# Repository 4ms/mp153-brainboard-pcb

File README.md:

## MP153 Brainboard

This is a small PCB with an STM32MP153 microprocessor, 512MB DDR3 RAM, and a stereo codec.
It's designed for running high-end audio projects.

The processor is a dual-core Cortex-A7 at 800MHz with a 240MHz Cortex-M4 co-processor. The RAM runs up to 533MHz.
The processor supports NEON instructions, so it can be very fast for audio applications.

The brainboard is meant to plug into a larger board that has all the controls and jacks. The pinout
is similar to the Daisy Submodule, though care should be taken to confirm this before plugging into an
untested project.

Look at the schematic, under "CONNECTORS". The four 2x5 pin 0.1" headers in
that section (JA1, JB1, JC1, JD1) are the connections to your control board. 

The bare minimum connection would be to apply +12V, GND, and -12V to the appropriate pins on header JA1.
The audio inputs and outputs are on header JB1, and should be in the range of +/- 10V.

Pots or other analog inputs in the range of 0V-3.3V can be input into any ADC-IN pin (most are on JC1).
Other peripherals are available: SPI, SDMMC, UART, I2C.

The debug header is J2 and you can select SWD or JTAG. I've had better luck with JTAG, so this is the default,
but if you need to use SWD then cut the solder jumper JP1 and blob it to the NRST side.

There's an on-board USB jack, and the USB signals are on pins, so you can have a USB High Speed jack on your panel or main board (Thanks Manu!).
Don't use both at once.

For firmware, look at https://github.com/4ms/mp1-brainboard-demo and also at https://github.com/4ms/stm32mp1-baremetal

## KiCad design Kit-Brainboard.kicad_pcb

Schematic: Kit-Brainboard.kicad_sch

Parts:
AN1: Pins_01x06_RightAngle_P2.54mm_TH; Pins_1x06_P2.54mm_Horizontal_TH_CroppedSilk; Part Number TSW-106-08-T-S-RA
C1, C19, C20, C41, C47, C48, C49: 2.2uF_0603_25V; C_0603; Part Number GRM188R6YA225KA12D; JLCPCB ID C57895
C2, C12, C21, C30, C40, C42, C43, C61, C64, C67, C68, C69, C82, C87, C92, C93, C94, C95, C98, C99, C102, C103, C106: 100nF_0402_16V; C_0402; Part Number GCM155R71C104KA55D; JLCPCB ID C1525
C3, C44, C81, C83: 10uF_0603_10V; C_0603; Part Number GRM188R61A106KE69D; JLCPCB ID C19702
C4: 22uF_0805_10V; C_0805; Part Number LMK212BBJ226MG-T; JLCPCB ID C45783
C5: 0.1uF_0603_16V; C_0603; Part Number 0603YC104KAT2A; JLCPCB ID C14663
C6, C7: 820pF_0402_10v; C_0402; Part Number 0402ZC821KAT2A; JLCPCB ID C565563
C8, C9, C10, C11: 180pF_0402_25V; C_0402; Part Number GRM1555C2A181JE01D; JLCPCB ID C106999
C13, C14: 6.8pF_0402_25V; C_0402; Part Number CC0402CRNPO9BN6R8; JLCPCB ID C1576
C15, C16, C17, C18, C24, C25, C26, C27, C28, C34, C35, C36, C37, C38, C39: 10nF_0402_16V; C_0402; Part Number CC0402KRX7R7BB103; JLCPCB ID C15195
C22, C23: 220pF_0402_50V; C_0402; Part Number AC0402JPNPO9BN221; JLCPCB ID C327000
C29, C32: 2.2uF_0402_6.3V; C_0402; Part Number GRM155R60J225KE95D; JLCPCB ID C12530
C31, C33, C45, C46, C50, C51, C52, C53, C54, C55, C59, C60, C62, C63, C70, C73, C79, C109: 1uF_0402_25V; C_0402; Part Number GMK105CC6105KV-F; JLCPCB ID C52923
C56, C57, C58, C65, C66, C72, C75, C77, C78, C85, C86, C96, C97, C100, C101, C104, C105, C107, C108: 100nF_0402_50V; C_0402; Part Number GRM155R71H104KE14D; JLCPCB ID C307331
C71, C74, C80: 3.3nF_0402_16V; C_0402; Part Number VJ0402Y332KXACW1BC; JLCPCB ID C26404
C76, C84: 4.7uF_0402_6.3V; C_0402; Part Number GRM155R60J475ME47; JLCPCB ID C23733
C88, C89, C90, C91: 22uF_0603_6.3V; C_0603; Part Number GRM188R60J226MEA0J; JLCPCB ID C59461
D1, D2, D3, D4, D5, D6, D7, D8, D9, D10, D12, D13, D14, D15, D16, D17, D18, D19, D20, D21, D22, D23, D24, D25: BAT54S; SOT23-3_PO132; Part Number BAT54S-7-F; JLCPCB ID C83574
D11: BAT54LP; DFN-1006-2; Part Number BAT54LP-7; JLCPCB ID C134410
J1: Pins_02x04_RightAngle_P2.54mm_TH; Pins_2x04_P2.54mm_Horizontal_CroppedSilk; Part Number TSW-104-08-T-D-RA
J2: Pins_02x05_P1.27mm_SMT; Pins_2x05_1.27mm_SMD; Part Number FTSH-105-01-F-DV
J3: USB_B_Micro_10118194-0011LF; USB_Micro-B_Amphenol_10118194_Horizontal; Part Number 10118194-0011LF
JA1: Pins_02x05_P2.54mm_SMT; PinHeader_2x05_P2.54mm_Vertical_SMD; Part Number TSM-105-01-F-DV
JB1: Pins_02x05_P2.54mm_SMT; PinHeader_2x05_P2.54mm_Vertical_SMD; Part Number TSM-105-01-F-DV
JC1: Pins_02x05_P2.54mm_SMT; PinHeader_2x05_P2.54mm_Vertical_SMD; Part Number TSM-105-01-F-DV
JD1: Conn_02x06_Odd_Even; PinHeader_2x06_P2.54mm_Vertical_SMD
JP1: SolderJumper_3_Bridged12; JUMPER_SMD_1x3_tiny
L1, L3: 1uH_3.2A_2520; L_1008_2520Metric; Part Number DFE252012P-1R0M=P2; JLCPCB ID C435392
L2: 4.7uH_1.7A_2510; L_Wuerth_MAPI-2510; Part Number SRN2510F-4R7M; JLCPCB ID C2047781
NT1, NT2: NetTie_2; NetTie-2_SMD_Pad0.16mm_6mil
PCB1: PCB; Part Number brainboard-mp1-v1.0
Q1: MMBT3904; SOT23-3_PO132; Part Number MMBT3904-TP; JLCPCB ID C20526
R1, R2: 4.7k_0402; R_0402; Part Number RC0402FR-074K7L; JLCPCB ID C105871
R3: 3k_0402; R_0402; Part Number RC0402FR-073KL; JLCPCB ID C137987
R4: 430k_0402; R_0402; Part Number RC0402FR-07430KL; JLCPCB ID C163463
R5: 620k_0402; R_0402; Part Number RC0402FR-07620KL; JLCPCB ID C137952
R6, R7, R8, R9, R10, R11, R13, R14, R30, R35, R36, R37, R38, R41, R46, R47, R48, R49, R50, R51, R61, R64, R66, R67, R69, R72, R74: 10k_0402; R_0402; Part Number RC0402FR-0710KL; JLCPCB ID C60490
R12, R15, R16, R17: 24k_0402; R_0402; Part Number RC0402FR-0724KL; JLCPCB ID C138026
R18, R19, R26, R27, R39, R40, R70, R71: 1k_0402; R_0402; Part Number RC0402FR-071KL; JLCPCB ID C106235
R20, R21, R22, R23, R24, R25: 2k_0402; R_0402; Part Number RC0402FR-072KL; JLCPCB ID C60488
R28, R29: 1M_0402; R_0402; Part Number RC0402FR-071ML; JLCPCB ID C138033
R31, R32, R60, R73: 100k_0402; R_0402; Part Number RC0402FR-07100KL; JLCPCB ID C60491
R33, R34: 14k_0402; R_0402; Part Number RC0402FR-0714KL; JLCPCB ID C327372
R42, R43, R44, R45, R53, R54, R55, R56, R57, R58: 68Ω_0402; R_0402; Part Number RC0402FR-0768RL; JLCPCB ID C163455
R52, R59: 240Ω_0402; R_0402; Part Number RC0402FR-07240RL; JLCPCB ID C114755
R62: 20k_0402; R_0402; Part Number RC0402FR-0720KL; JLCPCB ID C93942
R63: 31.6k_0402; R_0402; Part Number RC0402FR-0731K6L; JLCPCB ID C276265
R65: 6.8k_0402; R_0402; Part Number RC0402FR-076K8L; JLCPCB ID C93940
R68: 100Ω_0402; R_0402; Part Number RC0402FR-07100RL; JLCPCB ID C106232
S1, S2, S3: SW_Push_PTS526 SM15 SMTR2 LFS; Button_Tact_PTS526; Part Number PTS526 SM15 SMTR2 LFS
SJ1, SJ2: Shunt Jumper; Part Number LL1044-1B
U1: PCM3060PW; TSSOP-28_4.4x9.7mm_P0.65mm; Part Number PCM3060PW
U2: STM32MP15xxAD; TFBGA-257_10x10mm_perP0.5_cntrP0.65; Part Number STM32MP153DAD; JLCPCB ID C1236719
U3: USBLC6-2SC6; SOT-23-6; Part Number USBLC6-2SC6; JLCPCB ID C2827654
U4, U6, U7, U8, U9, U10, U11, U12: NJM2068; TSSOP-8_4.4x3mm_Pitch0.65mm; Part Number NJM2068V-TE1
U5: NORFLASH_W25Q128JV; SOIC-8_5.28x4.9mm_Pitch1.27mm; Part Number W25Q128JVSIQ; JLCPCB ID C113767
U13: NCP51460SN33; SOT23-3_PO132; Part Number NCP51460SN33T1G; JLCPCB ID C233715
U14: DDR3L-RAM-4Gb_MT41K256M16TW; FBGA-96_Layout2x3x16_Body8x14_P0.8mm; Part Number MT41K256M16TW-107-P-V00H; JLCPCB ID C253882
U15, U16, U17: AP6230xZ6; SOT-563; Part Number AP62301Z6
U18, U19: TAR5S33; SOT-23-5; Part Number TAR5S33TE85LF; JLCPCB ID C2762700
U20: AP2411SN; DFN-6-1EP_2x2mm_P0.65mm_EP1x1.6mm; Part Number AP2411SN-7; JLCPCB ID C2149815
V1: AP2120N-5.0TRG1; SOT23-3_PO132; Part Number AP2120N-5.0TRG1
X1: 24MHz_8pF_2x1.6mm; Crystal_2.0x1.6mm_4pin; Part Number ECS-240-8-37-CKM-TR3; JLCPCB ID C1986107

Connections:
+3V3: C2.1, C12.1, C90.2, D1.2 (cathode), D2.2 (cathode), D3.2 (cathode), D4.2 (cathode), D5.2 (cathode), D6.2 (cathode), D7.2 (cathode), D8.2 (cathode), D9.2 (cathode), D10.2 (cathode), D12.2 (cathode), D13.2 (cathode), D14.2 (cathode), D15.2 (cathode), D16.2 (cathode), D17.2 (cathode), D18.2 (cathode), D19.2 (cathode), D20.2 (cathode), D21.2 (cathode), D22.2 (cathode), D23.2 (cathode), D24.2 (cathode), D25.2 (cathode), L2.2, R1.2, R2.2, R63.2, U1.7 (VDD), U5.8 (VCC)
+5VA: C3.1, U1.24 (VCC), V1.2 (VO)
+12V: C1.1, C41.1, C45.2, C46.2, C47.2, C48.2, C49.2, C57.1, C58.1, C77.1, C78.1, C96.1, C97.1, C104.1, C105.1, JA1.9, R60.1, U4.8 (V+), U6.8 (V+), U7.8 (V+), U8.8 (V+), U9.8 (V+), U10.8 (V+), U11.8 (V+), U12.8 (V+), U13.1 (VI), U15.1 (VIN), U16.1 (VIN), U17.1 (VIN), U18.5 (IN), U19.5 (IN), V1.3 (VI)
-12VA: C65.1, C66.1, C85.1, C86.1, C100.1, C101.1, C107.1, C108.1, JA1.1, U4.4 (V-), U6.4 (V-), U7.4 (V-), U8.4 (V-), U9.4 (V-), U10.4 (V-), U11.4 (V-), U12.4 (V-)
/A0: AN1.5, U2.1J1 (PA4)
/A1: AN1.2, U2.1H1 (PA5)
/A2: R44.2, U2.T3 (PA2)
/A3: R45.2, U2.W3 (PA6)
/A4: R53.2, U2.N2 (PA3)
/A5: R54.2, U2.W2 (PA7)
/A6: R55.2, U2.U2 (PB0)
/A7: R56.2, U2.V1 (PC5)
/A8: R57.2, U2.P3 (PC3)
/A9: R58.2, U2.U4 (PC0)
/ADC-IN0_DAC-OUT0: JC1.1, R35.1
/ADC-IN1_DAC-OUT1: JC1.2, R36.1
/ADC-IN2: JC1.3, R37.1
/ADC-IN3: JC1.4, R38.1
/ADC-IN4: JC1.5, R46.1
/ADC-IN5: JC1.6, R47.1
/ADC-IN6: JC1.7, R48.1
/ADC-IN7: JC1.8, R49.1
/ADC-IN8: JC1.9, R50.1
/ADC-IN9: JC1.10, R51.1
/AUDIO_IN1: JB1.7, R27.2
/AUDIO_IN2: JB1.5, R26.2
/AUDIO_OUT1: JB1.3, R18.1
/AUDIO_OUT2: JB1.1, R19.1
/BOOT0: R30.2, R73.1, S1.3, S1.4, U2.H3 (BOOT0)
/BOOT2: Q1.3 (C), R74.2, U2.H1 (BOOT2)
/CODEC_RESET: U1.15 (~RST), U2.C1 (PE12)
/D0: C15.1, D1.3 (AK), R20.2, U2.C6 (PA9)
/D1: C16.1, D2.3 (AK), R21.2, U2.E3 (PE13)
/D2: C17.1, D3.3 (AK), R22.2, U2.A3 (PB7)
/D3: C18.1, D4.3 (AK), R23.2, U2.B6 (PB4)
/D4: JD1.8, U2.1A5 (PD2)
/D5: D23.3 (AK), JD1.1, U2.U15 (PA11)
/D6: D18.3 (AK), JD1.2, U2.U5 (PB10)
/D7: D22.3 (AK), JD1.6, U2.P2 (PC2)
/D8: D20.3 (AK), JD1.4, U2.T2 (PC1)
/D9: JD1.10, U2.1B4 (PC12)
/D10: D5.3 (AK), R24.2, U2.B8 (PA8)
/D11: D25.3 (AK), JA1.3, U2.U1 (PB1)
/D12: D6.3 (AK), R25.2, U2.A10 (PE4)
/D13: D19.3 (AK), JB1.8, U2.A2 (PD1)
/D14: D24.3 (AK), JA1.5, U2.T1 (PA1)
/D15: D21.3 (AK), JB1.6, U2.C5 (PD0)
/D16: JD1.9, U2.A9 (PC8)
/D17: JD1.7, U2.B9 (PC9)
/D18: JD1.5, U2.B10 (PC10)
/D19: JD1.3, U2.C11
/D-IN0: JB1.2, R20.1
/D-IN1: JB1.4, R21.1
/D-IN2: JB1.10, R22.1
/D-IN3: JB1.9, R23.1
/D-IN10: JA1.4, R24.1
/D-IN12: JA1.6, R25.1
/DDR_A0: U2.G18 (DDR_A0), U14.N3 (A0)
/DDR_A1: U2.M19 (DDR_A1), U14.P7 (A1)
/DDR_A2: U2.F17 (DDR_A2), U14.P3 (A2)
/DDR_A3: U2.F19 (DDR_A3), U14.N2 (A3)
/DDR_A4: U2.R17 (DDR_A4), U14.P8 (A4)
/DDR_A5: U2.1C9 (DDR_A5), U14.P2 (A5)
/DDR_A6: U2.1G9 (DDR_A6), U14.R8 (A6)
/DDR_A7: U2.1A9 (DDR_A7), U14.R2 (A7)
/DDR_A8: U2.T17 (DDR_A8), U14.T8 (A8)
/DDR_A9: U2.E18 (DDR_A9), U14.R3 (A9)
/DDR_A10: U2.M17 (DDR_A10), U14.L7 (A10/AP)
/DDR_A11: U2.N19 (DDR_A11), U14.R7 (A11)
/DDR_A12: U2.M18 (DDR_A12), U14.N7 (A12/BC#)
/DDR_A13: U2.E17 (DDR_A13), U14.T3 (A13)
/DDR_A14: U2.N18 (DDR_A14), U14.T7 (A14)
/DDR_BA0: U2.G19 (DDR_BA0), U14.M2 (BA0)
/DDR_BA1: U2.P18 (DDR_BA1), U14.N8 (BA1)
/DDR_BA2: U2.H17 (DDR_BA2), U14.M3 (BA2)
/DDR_CASN: U2.J19 (DDR_CASN), U14.K3 (CAS#)
/DDR_CKE: R67.2, U2.P17 (DDR_CKE), U14.K9 (CKE)
/DDR_CLK_N: R68.2, U2.K18 (DDR_CLKN), U14.K7 (CK#)
/DDR_CLK_P: R68.1, U2.L17 (DDR_CLKP), U14.J7 (CK)
/DDR_CSN: U2.J17 (DDR_CSN), U14.L2 (CS#)
/DDR_DQ0: U2.A17 (DDR_DQ0), U14.C3 (DQU1)
/DDR_DQ1: U2.A18 (DDR_DQ1), U14.C2 (DQU3)
/DDR_DQ2: U2.C18 (DDR_DQ2), U14.A7 (DQU4)
/DDR_DQ3: U2.B16 (DDR_DQ3), U14.A3 (DQU7)
/DDR_DQ4: U2.D18 (DDR_DQ4), U14.B8 (DQU6)
/DDR_DQ5: U2.D19 (DDR_DQ5), U14.C8 (DQU2)
/DDR_DQ6: U2.C19 (DDR_DQ6), U14.D7 (DQU0)
/DDR_DQ7: U2.B17 (DDR_DQ7), U14.A2 (DQU5)
/DDR_DQ8: U2.R18 (DDR_DQ8), U14.F2 (DQL2)
/DDR_DQ9: U2.U19 (DDR_DQ9), U14.E3 (DQL0)
/DDR_DQ10: U2.T19 (DDR_DQ10), U14.G2 (DQL6)
/DDR_DQ11: U2.W18 (DDR_DQ11), U14.F7 (DQL1)
/DDR_DQ12: U2.W17 (DDR_DQ12), U14.H8 (DQL5)
/DDR_DQ13: U2.T18 (DDR_DQ13), U14.H3 (DQL4)
/DDR_DQ14: U2.U17 (DDR_DQ14), U14.H7 (DQL7)
/DDR_DQ15: U2.V17 (DDR_DQ15), U14.F8 (DQL3)
/DDR_DQM0: U2.C17 (DDR_DQM0), U14.D3 (DMU)
/DDR_DQM1: U2.V18 (DDR_DQM1), U14.E7 (DML)
/DDR_DQS0_N: U2.B18 (DDR_DQS0N), U14.B7 (DQSU#)
/DDR_DQS0_P: U2.B19 (DDR_DQS0P), U14.C7 (DQSU)
/DDR_DQS1_N: U2.U18 (DDR_DQS1N), U14.G3 (DQSL#)
/DDR_DQS1_P: U2.V19 (DDR_DQS1P), U14.F3 (DQSL)
/DDR_ODT: U2.H18 (DDR_ODT), U14.K1 (ODT)
/DDR_RASN: U2.1E9 (DDR_RASN), U14.J3 (RAS#)
/DDR_RESETN: R69.2, U2.C16 (DDR_RESETN), U14.T2 (RESET#)
/DDR_WEN: U2.J18 (DDR_WEN), U14.L3 (WE#)
/DEBUG2: J1.5, U2.D1 (PG12)
/DEBUG3: J1.7, U2.D2 (PE11)
/DFU_BOOT: R72.1, S3.4, U2.E1 (PD8)
/FLASH_CLK: U2.1J7 (PF10), U5.6 (CLK)
/FLASH_CS: U2.W11 (PB6), U5.1 (~CS)
/FLASH_IO0: U2.V8 (PF8), U5.5 (IO0/SI)
/FLASH_IO1: U2.V9 (PF9), U5.2 (IO1/SO)
/FLASH_IO2: U2.W7 (PF7), U5.3 (IO2/~WP)
/FLASH_IO3: U2.U10 (PF6), U5.7 (IO3/~HOLD/~RESET)
/I2C2_SCL: R1.1, U1.1 (MC/SCL/FMT), U2.B3 (PD7)
/I2C2_SDA: R2.1, U1.2 (MD/SDA/DEMP), U2.B1 (PG15)
/IN-L: R40.2, U1.25 (VINL)
/IN-R: R39.2, U1.26 (VINR)
/JTCK_SWCLK: J2.4, U2.A16 (JTCK-SWCLK)
/JTDI: J2.8, U2.B15 (JTDI)
/JTDO_SWO: J2.6, U2.A15 (JTDO-TRACESWO)
/JTMS_SWDIO: J2.2, U2.C15 (JTMS-SWDIO)
/JTRST: JP1.1 (A), U2.B14 (NJTRST)
/LIN+: R6.1, U1.20 (VOUTL+)
/LIN-: R7.1, U1.19 (VOUTL-)
/NRST: C21.2, D11.1 (K), JP1.3 (B), S2.3, S2.4, U2.E2 (NRST)
/NRST_CORE: C24.2, U2.J3 (NRST_CORE)
/PWR_ON: R41.1, U2.M2 (PWR_ON), U15.5 (EN)
/PWR_ONRST: D11.2 (A), R41.2, U16.5 (EN), U17.5 (EN)
/RIN+: R8.1, U1.18 (VOUTR+)
/RIN-: R9.1, U1.17 (VOUTR-)
/SAI_FS: U1.4 (LRCK1), U1.11 (LRCK2), U2.U14 (PD12)
/SAI_MCLK: U1.6 (SCKI1), U1.9 (SCKI2), U2.C2 (PE0)
/SAI_SCK: U1.5 (BCK1), U1.10 (BCK2), U2.U13 (PD13)
/SAI_SD_A: U1.12 (DIN), U2.U8 (PD11)
/SAI_SD_B: U1.3 (DOUT), U2.U7 (PG10)
/UART_RX: J1.3, U2.C10 (PC7)
/UART_TX: J1.1, U2.A4 (PC6)
/USB_HS_DM: U2.W10 (USB_DM2), U3.3 (I/O2)
/USB_HS_DP: U2.V10 (USB_DP2), U3.1 (I/O1)
/USB_RREF: R3.2, U2.1J8 (USB_RREF)
/USB_VBUS: R4.2, R5.1, U2.V16 (OTG_VBUS)
/USB_VBUS_JACK: J3.1 (VBUS), R4.1, U3.5 (VBUS)
/VCOM: C4.1, C5.1, U1.21 (VCOM), U6.5 (+), U7.5 (+)
GND: C2.2, C12.2, C13.1, C14.1, C15.2, C16.2, C17.2, C18.2, C21.1, C24.1, C25.2, C26.2, C27.2, C28.2, C29.1, C32.1, C34.2, C35.2, C36.2, C37.2, C38.2, C39.2, C40.1, C42.2, C43.2, C46.1, C47.1, C48.1, C49.1, C50.1, C51.1, C52.1, C53.1, C54.1, C55.1, C56.2, C57.2, C58.2, C59.1, C60.1, C61.1, C62.1, C63.1, C64.1, C65.2, C66.2, C70.1, C71.2, C73.1, C74.2, C75.2, C76.1, C77.2, C78.2, C79.1, C80.2, C81.1, C82.1, C83.1, C85.2, C86.2, C87.1, C88.1, C89.1, C90.1, C91.1, C92.2, C93.1, C94.2, C95.1, C96.2, C97.2, C98.2, C99.2, C100.2, C101.2, C102.2, C103.2, C104.2, C105.2, C106.2, C107.2, C108.2, C109.1, D1.1 (Anode), D2.1 (Anode), D3.1 (Anode), D4.1 (Anode), D5.1 (Anode), D6.1 (Anode), D7.1 (Anode), D8.1 (Anode), D9.1 (Anode), D10.1 (Anode), D12.1 (Anode), D13.1 (Anode), D14.1 (Anode), D15.1 (Anode), D16.1 (Anode), D17.1 (Anode), D18.1 (Anode), D19.1 (Anode), D20.1 (Anode), D21.1 (Anode), D22.1 (Anode), D23.1 (Anode), D24.1 (Anode), D25.1 (Anode), J1.2, J1.4, J1.6, J1.8, J2.3, J2.5, J2.9, J3.5 (GND), J3.6 (Shield), JA1.7, NT1.2, NT2.2, Q1.2 (E), R3.1, R5.2, R28.2, R29.2, R52.2, R59.1, R62.1, R64.1, R66.1, R67.1, R69.1, R71.2, R72.2, S1.1, S1.2, S2.1, S2.2, U1.8 (DGND), U1.27 (~MS/ADR/IFMD), U1.28 (MODE), U2.1A6 (VSS), U2.1B8 (VSS), U2.1C3 (VSS), U2.1C5 (VSS), U2.1C7 (VSS), U2.1D2 (VSS), U2.1D4 (VSS), U2.1D6 (VSS), U2.1E3 (VSS), U2.1E5 (VSS), U2.1E7 (VSS), U2.1F4 (VSS), U2.1F6 (VSS), U2.1G2 (VSS), U2.1G5 (VSS), U2.1G7 (VSS), U2.1H2 (VSS), U2.1H3 (VSS), U2.1H4 (VSS), U2.1H6 (VSS), U2.1H8 (VSS), U2.1J5 (VSS), U2.1J9 (VSS), U2.A1 (VSS), U2.A6 (VSS), U2.A19 (VSS), U2.C14 (VSS), U2.D17 (VSS), U2.F3 (VSS), U2.F18 (VSS), U2.G1 (VSS), U2.G17 (VSS), U2.K3 (BOOT1), U2.K17 (VSS), U2.K19 (VSS), U2.N1 (VSS), U2.N17 (VSS), U2.R19 (VSS), U2.U9 (VSS), U2.U11 (BYPASS_REG1V8), U2.W1 (VSS), U2.W5 (VSS), U2.W13 (VSS), U2.W19 (VSS), U3.2 (GND), U5.4 (GND), U14.A9 (VSS), U14.B1 (VSSQ), U14.B3 (VSS), U14.B9 (VSSQ), U14.D1 (VSSQ), U14.D8 (VSSQ), U14.E1 (VSS), U14.E2 (VSSQ), U14.E8 (VSSQ), U14.F9 (VSSQ), U14.G1 (VSSQ), U14.G8 (VSS), U14.G9 (VSSQ), U14.J2 (VSS), U14.J8 (VSS), U14.M1 (VSS), U14.M9 (VSS), U14.P1 (VSS), U14.P9 (VSS), U14.T1 (VSS), U14.T9 (VSS), U15.3 (GND), U16.3 (GND), U17.3 (GND), U19.2 (GND), U20.2 (GND), U20.7 (EP), X1.2, X1.4
GNDA: C1.2, C3.2, C4.2, C5.2, C9.1, C11.1, NT1.1, R12.1, R15.1, U1.16 (SGND), U1.22 (AGND2), U1.23 (AGND1), V1.1 (GND)
GNDADC: C30.2, C31.1, C33.1, C41.2, C44.2, C45.1, C72.2, C84.1, JA1.8, NT2.1, U2.1G1 (VSSA), U13.3 (GND), U18.2 (GND)
unnamed: AN1.1, C26.1, D8.3 (AK), R36.2, U8.5 (+)
unnamed: AN1.3, R43.2
unnamed: AN1.4, C25.1, D7.3 (AK), R35.2, U8.3 (+)
unnamed: AN1.6, R42.2
unnamed: C6.1, R6.2, R10.2, R16.2
unnamed: C6.2, R7.2, R11.2, R12.2
unnamed: C7.1, R8.2, R13.2, R17.2
unnamed: C7.2, R9.2, R14.2, R15.2
unnamed: C8.1, R16.1, R18.2, U4.1
unnamed: C10.1, R17.1, R19.2, U4.7
unnamed: C19.1, R32.2
unnamed: C20.1, R31.2
unnamed: C22.1, R33.1, R39.1, U7.7
unnamed: C23.1, R34.1, R40.1, U6.7
unnamed: C27.1, D9.3 (AK), R37.2, U9.3 (+)
unnamed: C28.1, D10.3 (AK), R38.2, U9.5 (+)
unnamed: C34.1, D12.3 (AK), R46.2, U10.3 (+)
unnamed: C35.1, D13.3 (AK), R47.2, U10.5 (+)
unnamed: C36.1, D14.3 (AK), R48.2, U11.3 (+)
unnamed: C37.1, D15.3 (AK), R49.2, U11.5 (+)
unnamed: C38.1, D16.3 (AK), R50.2, U12.3 (+)
unnamed: C39.1, D17.3 (AK), R51.2, U12.5 (+)
unnamed: J2.10, JP1.2 (C)
unnamed: Q1.1 (B), R73.2
unnamed: C13.2, U2.H2 (PH0-OSC_IN), X1.3
unnamed: C14.2, U2.J2 (PH1-OSC_OUT), X1.1
unnamed: C29.2, U2.1J6 (VDDA1V1_REG)
unnamed: R52.1, U2.1A8 (DDR_ZQ)
unnamed: C9.2, R11.1, U4.3 (+)
unnamed: C8.2, R10.1, U4.2 (-)
unnamed: C11.2, R14.1, U4.5 (+)
unnamed: C10.2, R13.1, U4.6 (-)
unnamed: R27.1, R29.1, U6.3 (+)
unnamed: C19.2, U6.1, U6.2 (-)
unnamed: C23.2, R32.1, R34.2, U6.6 (-)
unnamed: R26.1, R28.1, U7.3 (+)
unnamed: C20.2, U7.1, U7.2 (-)
unnamed: C22.2, R31.1, R33.2, U7.6 (-)
unnamed: R42.1, U8.1, U8.2 (-)
unnamed: R43.1, U8.6 (-), U8.7
unnamed: R44.1, U9.1, U9.2 (-)
unnamed: R45.1, U9.6 (-), U9.7
unnamed: R53.1, U10.1, U10.2 (-)
unnamed: R54.1, U10.6 (-), U10.7
unnamed: R55.1, U11.1, U11.2 (-)
unnamed: R56.1, U11.6 (-), U11.7
unnamed: R57.1, U12.1, U12.2 (-)
unnamed: R58.1, U12.6 (-), U12.7
unnamed: R59.2, U14.L8 (ZQ)
unnamed: C67.2, U15.4 (BST)
unnamed: R61.1, R62.2, U15.6 (FB)
unnamed: C67.1, L1.1, U15.2 (SW)
unnamed: C68.2, U16.4 (BST)
unnamed: R63.1, R64.2, U16.6 (FB)
unnamed: C68.1, L2.1, U16.2 (SW)
unnamed: C69.2, U17.4 (BST)
unnamed: R65.1, R66.2, U17.6 (FB)
unnamed: C69.1, L3.1, U17.2 (SW)
unnamed: C72.1, U18.3 (Noise)
unnamed: C56.1, R60.2, U19.1 (EN)
unnamed: C75.1, U19.3 (Noise)
USB_DM: J3.2 (D-), JD1.12, U3.4 (I/O2)
USB_DP: J3.3 (D+), JD1.11, U3.6 (I/O1)
VDD: C51.2, C54.2, C60.2, C63.2, C88.2, J2.1, R30.1, R74.1, S3.1, U2.1D1 (VBAT), U2.1E2 (VDD), U2.1F3 (VDD), U2.1G3 (VDD), U2.1G4 (VDD), U2.1J3 (VDD), U2.K2 (PDR_ON_CORE), U2.L3 (PDR_ON), U18.1 (EN), U19.4 (OUT), U20.1 (IN)
VDDA: C30.1, C31.2, C84.2, U2.1F1 (VDDA), U2.1F2 (VDDA), U18.4 (OUT)
VDDA_1V8: C32.2, U2.1H5 (VDDA1V8_REG), U20.3 (EN)
VDD_CORE: C50.2, C53.2, C59.2, C62.2, C70.2, C73.2, C79.2, C89.2, L1.2, R61.2, U2.1B3 (VDDCORE), U2.1B5 (VDDCORE), U2.1C4 (VDDCORE), U2.1C6 (VDDCORE), U2.1D3 (VDDCORE), U2.1D5 (VDDCORE), U2.1D7 (VDDCORE), U2.1E4 (VDDCORE), U2.1E6 (VDDCORE), U2.1E8 (VDDCORE), U2.1F5 (VDDCORE), U2.1F7 (VDDCORE), U2.1G6 (VDDCORE), U2.1G8 (VDDCORE)
VDD_DDR: C52.2, C55.2, C61.2, C64.2, C71.1, C74.1, C80.1, C81.2, C82.2, C83.2, C87.2, C91.2, C92.1, C93.2, C94.1, C95.2, C98.1, C99.1, C102.1, C103.1, C106.1, L3.2, R65.2, R70.1, U2.1B9 (VDDQ_DDR), U2.1D9 (VDDQ_DDR), U2.1F9 (VDDQ_DDR), U2.1H9 (VDDQ_DDR), U14.A1 (VDDQ), U14.A8 (VDDQ), U14.B2 (VDD), U14.C1 (VDDQ), U14.C9 (VDDQ), U14.D2 (VDDQ), U14.D9 (VDD), U14.E9 (VDDQ), U14.F1 (VDDQ), U14.G7 (VDD), U14.H2 (VDDQ), U14.H9 (VDDQ), U14.K2 (VDD), U14.K8 (VDD), U14.N1 (VDD), U14.N9 (VDD), U14.R1 (VDD), U14.R9 (VDD)
VDD_USB: C76.2, U2.1H7 (VDD3V3_USB), U20.5 (OUT)
VREF+: C33.2, C44.1, JA1.2, U2.M3 (VREF+), U13.2 (VO)
VREF_DDR: C40.2, C42.1, C43.1, C109.2, R70.2, R71.1, U2.W16 (DDR_VREF), U14.H1 (VREFDQ), U14.M8 (VREFCA)

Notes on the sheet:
SPI2_SCK
ASSEMBLY
SPI2_MISO
SPI2_MOSI
TIM
UART7_TX
POWER
I2C5_SCL
SDMMC_CMD
mp153
ADC-IN10
ADC-IN11
SDMMC_D1
SDMMC_D3
-DK2: R125 not fitted
SWD PROGRAMMING
I2C5_SDA
3.3V for peripherals Rank 2 140mA max/typ (est 43mA of 12V)
CONNECTORS
ADC-IN13
1.35V and 0.65V for DDR3 Turns on after Vddcore is stable Power cycle on reset Datasheet recommends 1.5uH (AP623) or 2.2uH (AP622)
UART4_RX
SPI2_NSS
UART4_TX
SDMMC_CLK
3.3V, Rank 3 VDD3V3_USB turns on when VDDA_1V8 is present, which is powered by VDD.
UART5_RX
ANALOG FRONT END
Analog 3.3V Turns on after Vdd
To connect to VDD_DDR power plane
NOTE: 8 more 0.1uF caps are required from VDD_CORE to GND
UART7_RX
AUDIO
ADC-IN12
PROCESSOR PORTS
BRAINBOARD
SDMMC_D0
Turn-on at EN=1.5V @100k/100nF: t = 1.3ms
1.2V, Rank 2 IDDCORE_{max} = 1050mA Should be 1.34V to enable 800MHz, but seems to work ok at 1.2V? Ratio for 1.2V: 2:1 Ratio for 1.34V: 1.48:1 or 1:0.675 (14.7k/10k) Datasheet recommends 1.5uH (AP623) or 2.2uH (AP622)
SDMMC_D2

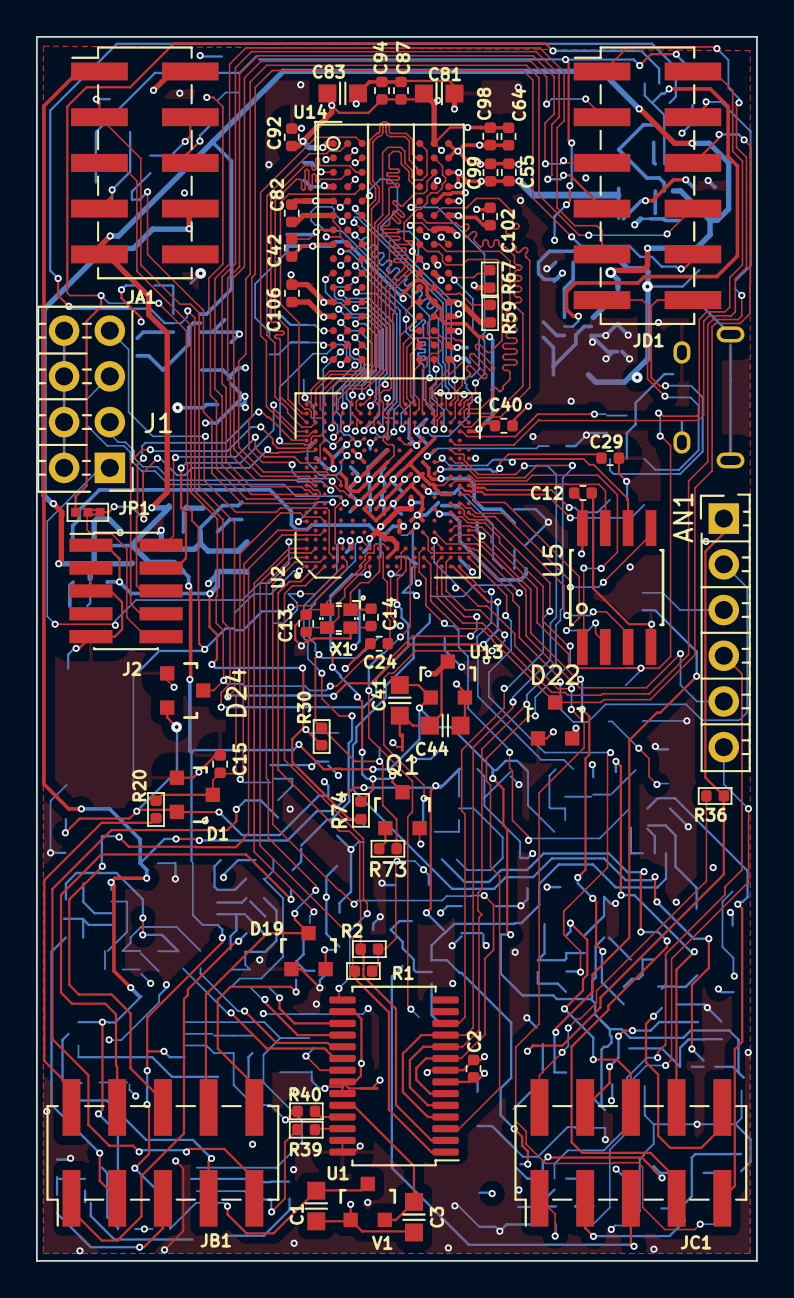
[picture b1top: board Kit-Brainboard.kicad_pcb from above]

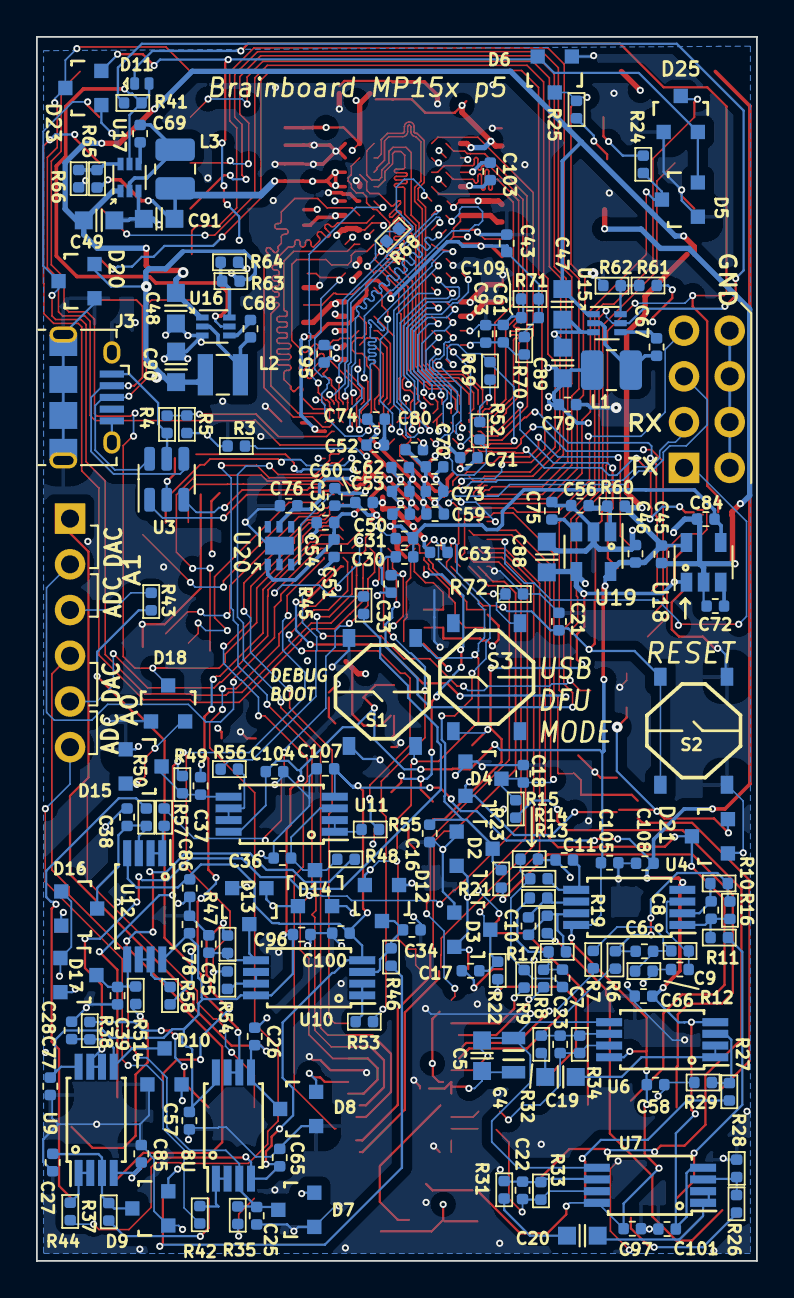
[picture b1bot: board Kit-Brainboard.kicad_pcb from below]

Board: 4 copper layers, 40.0 x 68.0 mm, 248 parts (190 on the bottom side), 219 nets.

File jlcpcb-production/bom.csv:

Designator,Footprint,Quantity,Value,LCSC Part #
AN1,Pins_1x06_P2.54mm_Horizontal_TH_CroppedSilk,1,Pins_01x06_RightAngle_P2.54mm_TH,
"C1, C19, C20, C41, C47, C48, C49",C_0603,7,2.2uF_0603_25V,C57895
"C10, C11, C8, C9",C_0402,4,180pF_0402_25V,C106999
"C100, C101, C104, C105, C107, C108, C56, C57, C58, C65, C66, C72, C75, C77, C78, C85, C86, C96, C97",C_0402,19,100nF_0402_50V,C307331
"C102, C103, C106, C12, C2, C21, C30, C40, C42, C43, C61, C64, C67, C68, C69, C82, C87, C92, C93, C94, C95, C98, C99",C_0402,23,100nF_0402_16V,C1525
"C109, C31, C33, C45, C46, C50, C51, C52, C53, C54, C55, C59, C60, C62, C63, C70, C73, C79",C_0402,18,1uF_0402_25V,C52923
"C13, C14",C_0402,2,6.8pF_0402_25V,C1576
"C15, C16, C17, C18, C24, C25, C26, C27, C28, C34, C35, C36, C37, C38, C39",C_0402,15,10nF_0402_16V,C15195
"C22, C23",C_0402,2,220pF_0402_50V,C327000
"C29, C32",C_0402,2,2.2uF_0402_6.3V,C12530
"C3, C44, C81, C83",C_0603,4,10uF_0603_10V,C19702
C4,C_0805,1,22uF_0805_10V,C45783
C5,C_0603,1,0.1uF_0603_16V,C14663
"C6, C7",C_0402,2,820pF_0402_10v,C565563
"C71, C74, C80",C_0402,3,3.3nF_0402_16V,C26404
"C76, C84",C_0402,2,4.7uF_0402_6.3V,C23733
"C88, C89, C90, C91",C_0603,4,22uF_0603_6.3V,C59461
"D1, D10, D12, D13, D14, D15, D16, D17, D18, D19, D2, D20, D21, D22, D23, D24, D25, D3, D4, D5, D6, D7, D8, D9",SOT23-3_PO132,24,BAT54S,C83574
D11,DFN-1006-2,1,BAT54LP,C134410
J1,Pins_2x04_P2.54mm_Horizontal_CroppedSilk,1,Pins_02x04_RightAngle_P2.54mm_TH,
J2,Pins_2x05_1.27mm_SMD,1,Pins_02x05_P1.27mm_SMT,
J3,USB_Micro-B_Amphenol_10118194_Horizontal,1,USB_B_Micro_10118194-0011LF,
"JA1, JB1, JC1",PinHeader_2x05_P2.54mm_Vertical_SMD,3,Pins_02x05_P2.54mm_SMT,
JD1,PinHeader_2x06_P2.54mm_Vertical_SMD,1,Conn_02x06_Odd_Even,
"L1, L3",1008,2,1uH_3.2A_2520,C435392
L2,L_Wuerth_MAPI-2510,1,4.7uH_1.7A_2510,C2047781
Q1,SOT23-3_PO132,1,MMBT3904,C20526
"R1, R2",R_0402,2,4.7k_0402,C105871
"R10, R11, R13, R14, R30, R35, R36, R37, R38, R41, R46, R47, R48, R49, R50, R51, R6, R61, R64, R66, R67, R69, R7, R72, R74, R8, R9",R_0402,27,10k_0402,C60490
"R12, R15, R16, R17",R_0402,4,24k_0402,C138026
"R18, R19, R26, R27, R39, R40, R70, R71",R_0402,8,1k_0402,C106235
"R20, R21, R22, R23, R24, R25",R_0402,6,2k_0402,C60488
"R28, R29",R_0402,2,1M_0402,C138033
R3,R_0402,1,3k_0402,C137987
"R31, R32, R60, R73",R_0402,4,100k_0402,C60491
"R33, R34",R_0402,2,14k_0402,C327372
R4,R_0402,1,430k_0402,C163463
"R42, R43, R44, R45, R53, R54, R55, R56, R57, R58",R_0402,10,68Ω_0402,C163455
R5,R_0402,1,620k_0402,C137952
"R52, R59",R_0402,2,240Ω_0402,C114755
R62,R_0402,1,20k_0402,C93942
R63,R_0402,1,31.6k_0402,C276265
R65,R_0402,1,6.8k_0402,C93940
R68,R_0402,1,100Ω_0402,C106232
"S1, S2, S3",Button_Tact_PTS526,3,SW_Push_PTS526 SM15 SMTR2 LFS,
U1,TSSOP-28_4.4x9.7mm_P0.65mm,1,PCM3060PW,
"U10, U11, U12, U4, U6, U7, U8, U9",TSSOP-8_4.4x3mm_Pitch0.65mm,8,NJM2068,
U13,SOT23-3_PO132,1,NCP51460SN33,C233715 
U14,FBGA-96_Layout2x3x16_Body8x14_P0.8mm,1,DDR3L-RAM-4Gb_MT41K256M16TW,C253882
"U15, U16, U17",SOT-563,3,AP6230xZ6,
"U18, U19",SOT-23-5,2,TAR5S33,C2762700
U2,TFBGA-257_10x10mm_perP0.5_cntrP0.65,1,STM32MP15xxAD,C1236719
U20,DFN-6-1EP_2x2mm_P0.65mm_EP1x1.6mm,1,AP2411SN,C2149815
U3,SOT-23-6,1,USBLC6-2SC6,C2827654
U5,SOIC-8_5.28x4.9mm_Pitch1.27mm,1,NORFLASH_W25Q128JV,C113767
V1,SOT23-3_PO132,1,AP2120N-5.0TRG1,
X1,Crystal_2.0x1.6mm_4pin,1,24MHz_8pF_2x1.6mm,C1986107

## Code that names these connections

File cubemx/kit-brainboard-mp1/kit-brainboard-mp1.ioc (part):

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Mcu.Name=STM32MP153DADx
Mcu.Package=TFBGA257
Mcu.UserName=STM32MP153DADx
PA0.Mode=IN16-Single-Ended
PA0.Signal=ADC1_INP16
PA1.Mode=IN17-Single-Ended
PA1.Signal=ADC1_INP17
PA10.Signal=GPIO_Input
PA11.Mode=I2C
PA11.Signal=I2C5_SCL
PA12.Mode=I2C
PA12.Signal=I2C5_SDA
PA15.Signal=GPIO_Input
PA2.Signal=ADCx_INP14
PA3.Signal=ADCx_INP15
PA4.Signal=ADCx_INP18
PA5.Signal=ADCx_INP19
PA6.Signal=ADCx_INP3
PA7.Signal=ADCx_INP7
PA8.Signal=GPIO_Input
PA9.Signal=GPIO_Input
PB0.Signal=ADCx_INP9
PB1.Signal=ADCx_INP5
PB10.Mode=Full_Duplex_Master
PB10.Signal=SPI2_SCK
PB12.Mode=NSS_Signal_Hard_Output
PB12.Signal=SPI2_NSS
PB15.Signal=GPIO_Input
PB6.Mode=Single Bank 1
PB6.Signal=QUADSPI_BK1_NCS
PB7.Signal=GPIO_Input
PC0.Signal=ADCx_INP10
PC1.Mode=Full_Duplex_Master
PC1.Signal=SPI2_MOSI
PC10.Mode=SD_4_bits_Wide_bus
PC10.Signal=SDMMC1_D2
PC11.Mode=SD_4_bits_Wide_bus
PC11.Signal=SDMMC1_D3
PC12.Mode=SD_4_bits_Wide_bus
PC12.Signal=SDMMC1_CK
PC2.Mode=Full_Duplex_Master
PC2.Signal=SPI2_MISO
PC3.Signal=ADCx_INP13
PC4.Signal=ADCx_INP4
PC5.Signal=ADCx_INP8
PC6.Mode=Asynchronous
PC6.Signal=USART6_TX
PC7.Mode=Asynchronous
PC7.Signal=USART6_RX
PC8.Mode=SD_4_bits_Wide_bus
PC8.Signal=SDMMC1_D0
PC9.Mode=SD_4_bits_Wide_bus
PC9.Signal=SDMMC1_D1
PD0.Mode=I2C
PD0.Signal=I2C6_SDA
PD1.Mode=I2C
PD1.Signal=I2C6_SCL
PD11.Mode=SAI_A_MasterWithClock
PD11.Signal=SAI2_SD_A
PD12.Mode=SAI_A_MasterWithClock
PD12.Signal=SAI2_FS_A
PD13.Mode=SAI_A_MasterWithClock
PD13.Signal=SAI2_SCK_A
PD2.Mode=SD_4_bits_Wide_bus
PD2.Signal=SDMMC1_CMD
PE0.Mode=SAI_A_MasterWithClock
PE0.Signal=SAI2_MCLK_A
PE10.GPIOParameters=GPIO_Label
PE10.GPIO_Label=CodecReset
PE10.Signal=GPIO_Output
PE11.Signal=GPIO_Output
PF10.Mode=Single Bank 1
PF10.Signal=QUADSPI_CLK
PF6.Mode=Single Bank 1
PF6.Signal=QUADSPI_BK1_IO3
PF7.Mode=Single Bank 1
PF7.Signal=QUADSPI_BK1_IO2
PF8.Mode=Single Bank 1
PF8.Signal=QUADSPI_BK1_IO0
PF9.Mode=Single Bank 1
PF9.Signal=QUADSPI_BK1_IO1
PG10.Mode=SAI_B_SyncSlave
PG10.Signal=SAI2_SD_B
PG8.Signal=GPIO_Output
PH0-OSC_IN.Mode=HSE-External-Clock-Source
PH0-OSC_IN.Signal=RCC_OSC_IN
PH1-OSC_OUT.Mode=HSE-External-Clock-Source
PH1-OSC_OUT.Signal=RCC_OSC_OUT
RCC.HSE_VALUE=24000000
board=custom

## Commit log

2025-01-13 Add p5 board
2025-01-13 README
2025-01-23 Added USB pins: Changed JD4 to 2x6 header
